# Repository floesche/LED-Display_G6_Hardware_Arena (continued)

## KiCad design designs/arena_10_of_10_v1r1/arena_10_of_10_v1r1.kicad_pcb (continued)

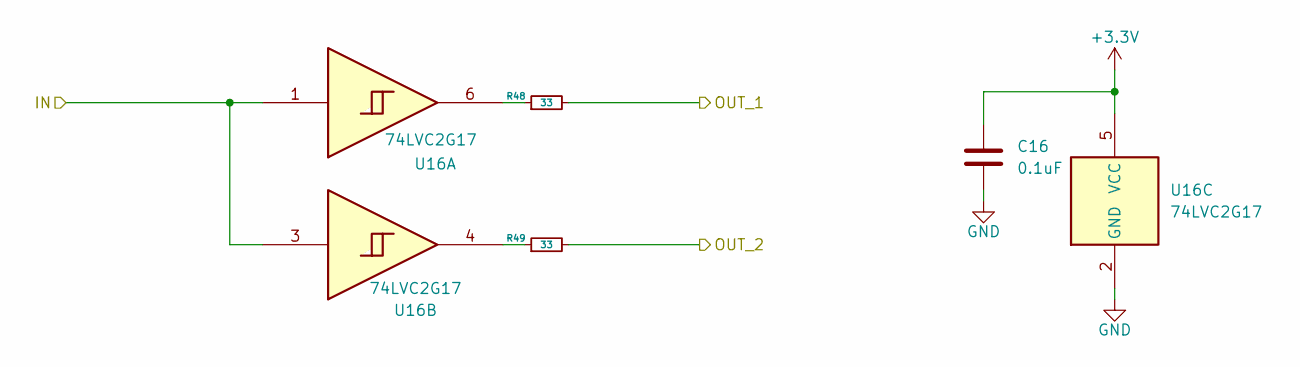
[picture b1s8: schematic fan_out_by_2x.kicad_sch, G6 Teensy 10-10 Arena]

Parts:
C16: 0.1uF; C_0402_1005Metric; LCSC Part # C1525
R48, R49: 33; R_0402_1005Metric; LCSC Part # C25105
U16: 74LVC2G17; SOT-23-6; LCSC Part # C7394037

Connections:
+3.3V: C16.1, U16.5 (VCC); also elsewhere on the board
/Fan Out/PAN.CS_00_P1: R48.2; also elsewhere on the board
/Fan Out/PAN.CS_00_P6: R49.2; also elsewhere on the board
/Fan Out/TNY.CS_00: U16.1, U16.3; also elsewhere on the board
unnamed: R48.1, U16.6
unnamed: R49.1, U16.4

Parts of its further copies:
C17, C18, C19, C20, C21, C22, C23, C24, C25, C26, C27, C28, C29, C30, C31, C32, C33, C34, C35: 0.1uF; C_0402_1005Metric; LCSC Part # C1525
R50, R51, R52, R53, R54, R55, R56, R57, R58, R59, R60, R61, R62, R63, R64, R65, R66, R67, R68, R69, R70, R71, R72, R73, R74, R75, R76, R77, R78, R79, R80, R81, R82, R83, R84, R85, R86, R87: 33; R_0402_1005Metric; LCSC Part # C25105
U17, U18, U19, U20, U21, U22, U23, U24, U25, U26, U27, U28, U29, U30, U31, U32, U33, U34, U35: 74LVC2G17; SOT-23-6; LCSC Part # C7394037

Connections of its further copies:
+3.3V: C17.1, C18.1, C19.1, C20.1, C21.1, C22.1, C23.1, C24.1, C25.1, C26.1, C27.1, C28.1, C29.1, C30.1, C31.1, C32.1, C33.1, C34.1, C35.1, U17.5 (VCC), U18.5 (VCC), U19.5 (VCC), U20.5 (VCC), U21.5 (VCC), U22.5 (VCC), U23.5 (VCC), U24.5 (VCC), U25.5 (VCC), U26.5 (VCC), U27.5 (VCC), U28.5 (VCC), U29.5 (VCC), U30.5 (VCC), U31.5 (VCC), U32.5 (VCC), U33.5 (VCC), U34.5 (VCC), U35.5 (VCC); also elsewhere on the board
/Fan Out/PAN.CS_01_P1: R50.2; also elsewhere on the board
/Fan Out/PAN.CS_01_P6: R51.2; also elsewhere on the board
/Fan Out/PAN.CS_02_P1: R52.2; also elsewhere on the board
/Fan Out/PAN.CS_02_P6: R53.2; also elsewhere on the board
/Fan Out/PAN.CS_03_P1: R54.2; also elsewhere on the board
/Fan Out/PAN.CS_03_P6: R55.2; also elsewhere on the board
/Fan Out/PAN.CS_04_P2: R56.2; also elsewhere on the board
/Fan Out/PAN.CS_04_P7: R57.2; also elsewhere on the board
/Fan Out/PAN.CS_05_P2: R58.2; also elsewhere on the board
/Fan Out/PAN.CS_05_P7: R59.2; also elsewhere on the board
/Fan Out/PAN.CS_06_P2: R60.2; also elsewhere on the board
/Fan Out/PAN.CS_06_P7: R61.2; also elsewhere on the board
/Fan Out/PAN.CS_07_P2: R62.2; also elsewhere on the board
/Fan Out/PAN.CS_07_P7: R63.2; also elsewhere on the board
/Fan Out/PAN.CS_08_P3: R64.2; also elsewhere on the board
/Fan Out/PAN.CS_08_P8: R65.2; also elsewhere on the board
/Fan Out/PAN.CS_09_P3: R66.2; also elsewhere on the board
/Fan Out/PAN.CS_09_P8: R67.2; also elsewhere on the board
/Fan Out/PAN.CS_10_P3: R68.2; also elsewhere on the board
/Fan Out/PAN.CS_10_P8: R69.2; also elsewhere on the board
/Fan Out/PAN.CS_11_P3: R70.2; also elsewhere on the board
/Fan Out/PAN.CS_11_P8: R71.2; also elsewhere on the board
/Fan Out/PAN.CS_12_P4: R72.2; also elsewhere on the board
/Fan Out/PAN.CS_12_P9: R73.2; also elsewhere on the board
/Fan Out/PAN.CS_13_P4: R74.2; also elsewhere on the board
/Fan Out/PAN.CS_13_P9: R75.2; also elsewhere on the board
/Fan Out/PAN.CS_14_P4: R76.2; also elsewhere on the board
/Fan Out/PAN.CS_14_P9: R77.2; also elsewhere on the board
/Fan Out/PAN.CS_15_P4: R78.2; also elsewhere on the board
/Fan Out/PAN.CS_15_P9: R79.2; also elsewhere on the board
/Fan Out/PAN.CS_16_P5: R80.2; also elsewhere on the board
/Fan Out/PAN.CS_16_P10: R81.2; also elsewhere on the board
/Fan Out/PAN.CS_17_P5: R82.2; also elsewhere on the board
/Fan Out/PAN.CS_17_P10: R83.2; also elsewhere on the board
/Fan Out/PAN.CS_18_P5: R84.2; also elsewhere on the board
/Fan Out/PAN.CS_18_P10: R85.2; also elsewhere on the board
/Fan Out/PAN.CS_19_P5: R86.2; also elsewhere on the board
/Fan Out/PAN.CS_19_P10: R87.2; also elsewhere on the board
/Fan Out/TNY.CS_01: U17.1, U17.3; also elsewhere on the board
/Fan Out/TNY.CS_02: U18.1, U18.3; also elsewhere on the board
/Fan Out/TNY.CS_03: U19.1, U19.3; also elsewhere on the board
/Fan Out/TNY.CS_04: U20.1, U20.3; also elsewhere on the board
/Fan Out/TNY.CS_05: U21.1, U21.3; also elsewhere on the board
/Fan Out/TNY.CS_06: U22.1, U22.3; also elsewhere on the board
/Fan Out/TNY.CS_07: U23.1, U23.3; also elsewhere on the board
/Fan Out/TNY.CS_08: U24.1, U24.3; also elsewhere on the board
/Fan Out/TNY.CS_09: U25.1, U25.3; also elsewhere on the board
/Fan Out/TNY.CS_10: U26.1, U26.3; also elsewhere on the board
/Fan Out/TNY.CS_11: U27.1, U27.3; also elsewhere on the board
/Fan Out/TNY.CS_12: U28.1, U28.3; also elsewhere on the board
/Fan Out/TNY.CS_13: U29.1, U29.3; also elsewhere on the board
/Fan Out/TNY.CS_14: U30.1, U30.3; also elsewhere on the board
/Fan Out/TNY.CS_15: U31.1, U31.3; also elsewhere on the board
/Fan Out/TNY.CS_16: U32.1, U32.3; also elsewhere on the board
/Fan Out/TNY.CS_17: U33.1, U33.3; also elsewhere on the board
/Fan Out/TNY.CS_18: U34.1, U34.3; also elsewhere on the board
/Fan Out/TNY.CS_19: U35.1, U35.3; also elsewhere on the board
unnamed: R50.1, U17.6
unnamed: R51.1, U17.4
unnamed: R52.1, U18.6
unnamed: R53.1, U18.4
unnamed: R54.1, U19.6
unnamed: R55.1, U19.4
unnamed: R56.1, U20.6
unnamed: R57.1, U20.4
unnamed: R58.1, U21.6
unnamed: R59.1, U21.4
unnamed: R60.1, U22.6
unnamed: R61.1, U22.4
unnamed: R62.1, U23.6
unnamed: R63.1, U23.4
unnamed: R64.1, U24.6
unnamed: R65.1, U24.4
unnamed: R66.1, U25.6
unnamed: R67.1, U25.4
unnamed: R68.1, U26.6
unnamed: R69.1, U26.4
unnamed: R70.1, U27.6
unnamed: R71.1, U27.4
unnamed: R72.1, U28.6
unnamed: R73.1, U28.4
unnamed: R74.1, U29.6
unnamed: R75.1, U29.4
unnamed: R76.1, U30.6
unnamed: R77.1, U30.4
unnamed: R78.1, U31.6
unnamed: R79.1, U31.4
unnamed: R80.1, U32.6
unnamed: R81.1, U32.4
unnamed: R82.1, U33.6
unnamed: R83.1, U33.4
unnamed: R84.1, U34.6
unnamed: R85.1, U34.4
unnamed: R86.1, U35.6
unnamed: R87.1, U35.4

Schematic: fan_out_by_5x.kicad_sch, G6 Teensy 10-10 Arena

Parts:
C4, C5, C6: 0.1uF; C_0402_1005Metric; LCSC Part # C1525
R28, R29, R30, R31, R32: 33; R_0402_1005Metric; LCSC Part # C25105
U4, U5, U6: 74LVC2G17; SOT-23-6; LCSC Part # C7394037

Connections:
+3.3V: C4.1, C5.1, C6.1, U4.5 (VCC), U5.5 (VCC), U6.5 (VCC); also elsewhere on the board
/Fan Out/PAN.SCK_B0_P1: R28.2; also elsewhere on the board
/Fan Out/PAN.SCK_B0_P2: R29.2; also elsewhere on the board
/Fan Out/PAN.SCK_B0_P3: R30.2; also elsewhere on the board
/Fan Out/PAN.SCK_B0_P4: R31.2; also elsewhere on the board
/Fan Out/PAN.SCK_B0_P5: R32.2; also elsewhere on the board
/Fan Out/TNY.SCK_B0: U4.1, U4.3, U5.1, U5.3, U6.1; also elsewhere on the board
unnamed: R28.1, U4.6
unnamed: R29.1, U4.4
unnamed: R30.1, U5.6
unnamed: R31.1, U5.4
unnamed: R32.1, U6.6

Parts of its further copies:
C7, C8, C9, C10, C11, C12, C13, C14, C15, C36, C37, C38, C39, C40, C41: 0.1uF; C_0402_1005Metric; LCSC Part # C1525
R33, R34, R35, R36, R37, R38, R39, R40, R41, R42, R43, R44, R45, R46, R47, R88, R89, R90, R91, R92, R93, R94, R95, R96, R97: 33; R_0402_1005Metric; LCSC Part # C25105
U7, U8, U9, U10, U11, U12, U13, U14, U15, U36, U37, U38, U39, U40, U41: 74LVC2G17; SOT-23-6; LCSC Part # C7394037

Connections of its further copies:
+3.3V: C7.1, C8.1, C9.1, C10.1, C11.1, C12.1, C13.1, C14.1, C15.1, C36.1, C37.1, C38.1, C39.1, C40.1, C41.1, U7.5 (VCC), U8.5 (VCC), U9.5 (VCC), U10.5 (VCC), U11.5 (VCC), U12.5 (VCC), U13.5 (VCC), U14.5 (VCC), U15.5 (VCC), U36.5 (VCC), U37.5 (VCC), U38.5 (VCC), U39.5 (VCC), U40.5 (VCC), U41.5 (VCC); also elsewhere on the board
/Fan Out/PAN.EINT_P1: R93.2; also elsewhere on the board
/Fan Out/PAN.EINT_P2: R94.2; also elsewhere on the board
/Fan Out/PAN.EINT_P3: R95.2; also elsewhere on the board
/Fan Out/PAN.EINT_P4: R96.2; also elsewhere on the board
/Fan Out/PAN.EINT_P5: R97.2; also elsewhere on the board
/Fan Out/PAN.EINT_P6: R88.2; also elsewhere on the board
/Fan Out/PAN.EINT_P7: R89.2; also elsewhere on the board
/Fan Out/PAN.EINT_P8: R90.2; also elsewhere on the board
/Fan Out/PAN.EINT_P9: R91.2; also elsewhere on the board
/Fan Out/PAN.EINT_P10: R92.2; also elsewhere on the board
/Fan Out/PAN.MOSI_B0_P1: R33.2; also elsewhere on the board
/Fan Out/PAN.MOSI_B0_P2: R34.2; also elsewhere on the board
/Fan Out/PAN.MOSI_B0_P3: R35.2; also elsewhere on the board
/Fan Out/PAN.MOSI_B0_P4: R36.2; also elsewhere on the board
/Fan Out/PAN.MOSI_B0_P5: R37.2; also elsewhere on the board
/Fan Out/PAN.MOSI_B1_P6: R43.2; also elsewhere on the board
/Fan Out/PAN.MOSI_B1_P7: R44.2; also elsewhere on the board
/Fan Out/PAN.MOSI_B1_P8: R45.2; also elsewhere on the board
/Fan Out/PAN.MOSI_B1_P9: R46.2; also elsewhere on the board
/Fan Out/PAN.MOSI_B1_P10: R47.2; also elsewhere on the board
/Fan Out/PAN.SCK_B1_P6: R38.2; also elsewhere on the board
/Fan Out/PAN.SCK_B1_P7: R39.2; also elsewhere on the board
/Fan Out/PAN.SCK_B1_P8: R40.2; also elsewhere on the board
/Fan Out/PAN.SCK_B1_P9: R41.2; also elsewhere on the board
/Fan Out/PAN.SCK_B1_P10: R42.2; also elsewhere on the board
/Fan Out/TNY.EINT: U36.1, U36.3, U37.1, U37.3, U38.1, U39.1, U39.3, U40.1, U40.3, U41.1; also elsewhere on the board
/Fan Out/TNY.MOSI_B0: U7.1, U7.3, U8.1, U8.3, U9.1; also elsewhere on the board
/Fan Out/TNY.MOSI_B1: U13.1, U13.3, U14.1, U14.3, U15.1; also elsewhere on the board
/Fan Out/TNY.SCK_B1: U10.1, U10.3, U11.1, U11.3, U12.1; also elsewhere on the board
unnamed: R33.1, U7.6
unnamed: R34.1, U7.4
unnamed: R35.1, U8.6
unnamed: R36.1, U8.4
unnamed: R37.1, U9.6
unnamed: R38.1, U10.6
unnamed: R39.1, U10.4
unnamed: R40.1, U11.6
unnamed: R41.1, U11.4
unnamed: R42.1, U12.6
unnamed: R43.1, U13.6
unnamed: R44.1, U13.4
unnamed: R45.1, U14.6
unnamed: R46.1, U14.4
unnamed: R47.1, U15.6
unnamed: R88.1, U36.6
unnamed: R89.1, U36.4
unnamed: R90.1, U37.6
unnamed: R91.1, U37.4
unnamed: R92.1, U38.6
unnamed: R93.1, U39.6
unnamed: R94.1, U39.4
unnamed: R95.1, U40.6
unnamed: R96.1, U40.4
unnamed: R97.1, U41.6

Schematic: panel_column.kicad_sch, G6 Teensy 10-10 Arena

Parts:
C42: 100uF; C_1210_3225Metric; LCSC Part # C7432790
J5, J6: Conn_01x05; PinSocket_1x05_P2.54mm_Vertical; LCSC Part # C50950
P1: NA; Panel_Silk; not fitted

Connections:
/Panels/Panel Column P1/Column Buffer/CS0_OUT: J6.1; also elsewhere on the board
/Panels/Panel Column P1/Column Buffer/CS1_OUT: J6.2; also elsewhere on the board
/Panels/Panel Column P1/Column Buffer/CS2_OUT: J6.3; also elsewhere on the board
/Panels/Panel Column P1/Column Buffer/CS_3OUT: J6.4; also elsewhere on the board
/Panels/Panel Column P1/Column Buffer/EINT_OUT: J6.5; also elsewhere on the board
/Panels/Panel Column P1/Column Buffer/MISO_IN: J5.5; also elsewhere on the board
/Panels/Panel Column P1/Column Buffer/MOSI_OUT: J5.4; also elsewhere on the board
/Panels/Panel Column P1/Column Buffer/SCK_OUT: J5.3; also elsewhere on the board

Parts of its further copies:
C47, C52, C57, C62, C67, C72, C77, C82, C87: 100uF; C_1210_3225Metric; LCSC Part # C7432790
J7, J8, J9, J10, J11, J12, J13, J14, J15, J16, J17, J18, J19, J20, J21, J22, J23, J24: Conn_01x05; PinSocket_1x05_P2.54mm_Vertical; LCSC Part # C50950
P2, P3, P4, P5, P6, P7, P8, P9, P10: NA; Panel_Silk; not fitted

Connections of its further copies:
/Panels/Panel Column P2/Column Buffer/CS0_OUT: J8.1; also elsewhere on the board
/Panels/Panel Column P2/Column Buffer/CS1_OUT: J8.2; also elsewhere on the board
/Panels/Panel Column P2/Column Buffer/CS2_OUT: J8.3; also elsewhere on the board
/Panels/Panel Column P2/Column Buffer/CS_3OUT: J8.4; also elsewhere on the board
/Panels/Panel Column P2/Column Buffer/EINT_OUT: J8.5; also elsewhere on the board
/Panels/Panel Column P2/Column Buffer/MISO_IN: J7.5; also elsewhere on the board
/Panels/Panel Column P2/Column Buffer/MOSI_OUT: J7.4; also elsewhere on the board
/Panels/Panel Column P2/Column Buffer/SCK_OUT: J7.3; also elsewhere on the board
/Panels/Panel Column P3/Column Buffer/CS0_OUT: J10.1; also elsewhere on the board
/Panels/Panel Column P3/Column Buffer/CS1_OUT: J10.2; also elsewhere on the board
/Panels/Panel Column P3/Column Buffer/CS2_OUT: J10.3; also elsewhere on the board
/Panels/Panel Column P3/Column Buffer/CS_3OUT: J10.4; also elsewhere on the board
/Panels/Panel Column P3/Column Buffer/EINT_OUT: J10.5; also elsewhere on the board
/Panels/Panel Column P3/Column Buffer/MISO_IN: J9.5; also elsewhere on the board
/Panels/Panel Column P3/Column Buffer/MOSI_OUT: J9.4; also elsewhere on the board
/Panels/Panel Column P3/Column Buffer/SCK_OUT: J9.3; also elsewhere on the board
/Panels/Panel Column P4/Column Buffer/CS0_OUT: J12.1; also elsewhere on the board
/Panels/Panel Column P4/Column Buffer/CS1_OUT: J12.2; also elsewhere on the board
/Panels/Panel Column P4/Column Buffer/CS2_OUT: J12.3; also elsewhere on the board
/Panels/Panel Column P4/Column Buffer/CS_3OUT: J12.4; also elsewhere on the board
/Panels/Panel Column P4/Column Buffer/EINT_OUT: J12.5; also elsewhere on the board
/Panels/Panel Column P4/Column Buffer/MISO_IN: J11.5; also elsewhere on the board
/Panels/Panel Column P4/Column Buffer/MOSI_OUT: J11.4; also elsewhere on the board
/Panels/Panel Column P4/Column Buffer/SCK_OUT: J11.3; also elsewhere on the board
/Panels/Panel Column P5/Column Buffer/CS0_OUT: J14.1; also elsewhere on the board
/Panels/Panel Column P5/Column Buffer/CS1_OUT: J14.2; also elsewhere on the board
/Panels/Panel Column P5/Column Buffer/CS2_OUT: J14.3; also elsewhere on the board
/Panels/Panel Column P5/Column Buffer/CS_3OUT: J14.4; also elsewhere on the board
/Panels/Panel Column P5/Column Buffer/EINT_OUT: J14.5; also elsewhere on the board
/Panels/Panel Column P5/Column Buffer/MISO_IN: J13.5; also elsewhere on the board
/Panels/Panel Column P5/Column Buffer/MOSI_OUT: J13.4; also elsewhere on the board
/Panels/Panel Column P5/Column Buffer/SCK_OUT: J13.3; also elsewhere on the board
/Panels/Panel Column P6/Column Buffer/CS0_OUT: J16.1; also elsewhere on the board
/Panels/Panel Column P6/Column Buffer/CS1_OUT: J16.2; also elsewhere on the board
/Panels/Panel Column P6/Column Buffer/CS2_OUT: J16.3; also elsewhere on the board
/Panels/Panel Column P6/Column Buffer/CS_3OUT: J16.4; also elsewhere on the board
/Panels/Panel Column P6/Column Buffer/EINT_OUT: J16.5; also elsewhere on the board
/Panels/Panel Column P6/Column Buffer/MISO_IN: J15.5; also elsewhere on the board
/Panels/Panel Column P6/Column Buffer/MOSI_OUT: J15.4; also elsewhere on the board
/Panels/Panel Column P6/Column Buffer/SCK_OUT: J15.3; also elsewhere on the board
/Panels/Panel Column P7/Column Buffer/CS0_OUT: J18.1; also elsewhere on the board
/Panels/Panel Column P7/Column Buffer/CS1_OUT: J18.2; also elsewhere on the board
/Panels/Panel Column P7/Column Buffer/CS2_OUT: J18.3; also elsewhere on the board
/Panels/Panel Column P7/Column Buffer/CS_3OUT: J18.4; also elsewhere on the board
/Panels/Panel Column P7/Column Buffer/EINT_OUT: J18.5; also elsewhere on the board
/Panels/Panel Column P7/Column Buffer/MISO_IN: J17.5; also elsewhere on the board
/Panels/Panel Column P7/Column Buffer/MOSI_OUT: J17.4; also elsewhere on the board
/Panels/Panel Column P7/Column Buffer/SCK_OUT: J17.3; also elsewhere on the board
/Panels/Panel Column P8/Column Buffer/CS0_OUT: J20.1; also elsewhere on the board
/Panels/Panel Column P8/Column Buffer/CS1_OUT: J20.2; also elsewhere on the board
/Panels/Panel Column P8/Column Buffer/CS2_OUT: J20.3; also elsewhere on the board
/Panels/Panel Column P8/Column Buffer/CS_3OUT: J20.4; also elsewhere on the board
/Panels/Panel Column P8/Column Buffer/EINT_OUT: J20.5; also elsewhere on the board
/Panels/Panel Column P8/Column Buffer/MISO_IN: J19.5; also elsewhere on the board
/Panels/Panel Column P8/Column Buffer/MOSI_OUT: J19.4; also elsewhere on the board
/Panels/Panel Column P8/Column Buffer/SCK_OUT: J19.3; also elsewhere on the board
/Panels/Panel Column P9/Column Buffer/CS0_OUT: J22.1; also elsewhere on the board
/Panels/Panel Column P9/Column Buffer/CS1_OUT: J22.2; also elsewhere on the board
/Panels/Panel Column P9/Column Buffer/CS2_OUT: J22.3; also elsewhere on the board
/Panels/Panel Column P9/Column Buffer/CS_3OUT: J22.4; also elsewhere on the board
/Panels/Panel Column P9/Column Buffer/EINT_OUT: J22.5; also elsewhere on the board
/Panels/Panel Column P9/Column Buffer/MISO_IN: J21.5; also elsewhere on the board
/Panels/Panel Column P9/Column Buffer/MOSI_OUT: J21.4; also elsewhere on the board
/Panels/Panel Column P9/Column Buffer/SCK_OUT: J21.3; also elsewhere on the board
/Panels/Panel Column P10/Column Buffer/CS0_OUT: J24.1; also elsewhere on the board
/Panels/Panel Column P10/Column Buffer/CS1_OUT: J24.2; also elsewhere on the board
/Panels/Panel Column P10/Column Buffer/CS2_OUT: J24.3; also elsewhere on the board
/Panels/Panel Column P10/Column Buffer/CS_3OUT: J24.4; also elsewhere on the board
/Panels/Panel Column P10/Column Buffer/EINT_OUT: J24.5; also elsewhere on the board
/Panels/Panel Column P10/Column Buffer/MISO_IN: J23.5; also elsewhere on the board
/Panels/Panel Column P10/Column Buffer/MOSI_OUT: J23.4; also elsewhere on the board
/Panels/Panel Column P10/Column Buffer/SCK_OUT: J23.3; also elsewhere on the board

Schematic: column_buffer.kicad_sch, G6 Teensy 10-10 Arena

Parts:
C43, C44, C45, C46: 0.1uF; C_0402_1005Metric; LCSC Part # C1525
R98, R99, R100, R101, R102, R103, R104, R105: 33; R_0402_1005Metric; LCSC Part # C25105
U42, U43, U44, U45: 74LVC2G17; SOT-23-6; LCSC Part # C7394037

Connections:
+3.3V: C43.1, C44.1, C45.1, C46.1, U42.5 (VCC), U43.5 (VCC), U44.5 (VCC), U45.5 (VCC); also elsewhere on the board
/Fan Out/PAN.CS_00_P1: U43.3; also elsewhere on the board
/Fan Out/PAN.CS_01_P1: U44.1; also elsewhere on the board
/Fan Out/PAN.CS_02_P1: U44.3; also elsewhere on the board
/Fan Out/PAN.CS_03_P1: U45.1; also elsewhere on the board
/Fan Out/PAN.EINT_P1: U45.3; also elsewhere on the board
/Fan Out/PAN.MISO_B0_P1: R98.2; also elsewhere on the board
/Fan Out/PAN.MOSI_B0_P1: U42.3; also elsewhere on the board
/Fan Out/PAN.SCK_B0_P1: U42.1; also elsewhere on the board
/Panels/Panel Column P1/Column Buffer/CS0_OUT: R101.2; also elsewhere on the board
/Panels/Panel Column P1/Column Buffer/CS1_OUT: R102.2; also elsewhere on the board
/Panels/Panel Column P1/Column Buffer/CS2_OUT: R103.2; also elsewhere on the board
/Panels/Panel Column P1/Column Buffer/CS_3OUT: R104.2; also elsewhere on the board
/Panels/Panel Column P1/Column Buffer/EINT_OUT: R105.2; also elsewhere on the board
/Panels/Panel Column P1/Column Buffer/MISO_IN: U43.1; also elsewhere on the board
/Panels/Panel Column P1/Column Buffer/MOSI_OUT: R100.2; also elsewhere on the board
/Panels/Panel Column P1/Column Buffer/SCK_OUT: R99.2; also elsewhere on the board
unnamed: R98.1, U43.6
unnamed: R99.1, U42.6
unnamed: R100.1, U42.4
unnamed: R101.1, U43.4
unnamed: R102.1, U44.6
unnamed: R103.1, U44.4
unnamed: R104.1, U45.6
unnamed: R105.1, U45.4

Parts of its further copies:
C48, C49, C50, C51, C53, C54, C55, C56, C58, C59, C60, C61, C63, C64, C65, C66, C68, C69, C70, C71, C73, C74, C75, C76, C78, C79, C80, C81, C83, C84, C85, C86, C88, C89, C90, C91: 0.1uF; C_0402_1005Metric; LCSC Part # C1525
R106, R107, R108, R109, R110, R111, R112, R113, R114, R115, R116, R117, R118, R119, R120, R121, R122, R123, R124, R125, R126, R127, R128, R129, R130, R131, R132, R133, R134, R135, R136, R137, R138, R139, R140, R141, R142, R143, R144, R145, R146, R147, R148, R149, R150, R151, R152, R153, R154, R155, R156, R157, R158, R159, R160, R161, R162, R163, R164, R165, R166, R167, R168, R169, R170, R171, R172, R173, R174, R175, R176, R177: 33; R_0402_1005Metric; LCSC Part # C25105
U46, U47, U48, U49, U50, U51, U52, U53, U54, U55, U56, U57, U58, U59, U60, U61, U62, U63, U64, U65, U66, U67, U68, U69, U70, U71, U72, U73, U74, U75, U76, U77, U78, U79, U80, U81: 74LVC2G17; SOT-23-6; LCSC Part # C7394037

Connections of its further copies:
+3.3V: C48.1, C49.1, C50.1, C51.1, C53.1, C54.1, C55.1, C56.1, C58.1, C59.1, C60.1, C61.1, C63.1, C64.1, C65.1, C66.1, C68.1, C69.1, C70.1, C71.1, C73.1, C74.1, C75.1, C76.1, C78.1, C79.1, C80.1, C81.1, C83.1, C84.1, C85.1, C86.1, C88.1, C89.1, C90.1, C91.1, U46.5 (VCC), U47.5 (VCC), U48.5 (VCC), U49.5 (VCC), U50.5 (VCC), U51.5 (VCC), U52.5 (VCC), U53.5 (VCC), U54.5 (VCC), U55.5 (VCC), U56.5 (VCC), U57.5 (VCC), U58.5 (VCC), U59.5 (VCC), U60.5 (VCC), U61.5 (VCC), U62.5 (VCC), U63.5 (VCC), U64.5 (VCC), U65.5 (VCC), U66.5 (VCC), U67.5 (VCC), U68.5 (VCC), U69.5 (VCC), U70.5 (VCC), U71.5 (VCC), U72.5 (VCC), U73.5 (VCC), U74.5 (VCC), U75.5 (VCC), U76.5 (VCC), U77.5 (VCC), U78.5 (VCC), U79.5 (VCC), U80.5 (VCC), U81.5 (VCC); also elsewhere on the board
/Fan Out/PAN.CS_00_P6: U63.3; also elsewhere on the board
/Fan Out/PAN.CS_01_P6: U64.1; also elsewhere on the board
/Fan Out/PAN.CS_02_P6: U64.3; also elsewhere on the board
/Fan Out/PAN.CS_03_P6: U65.1; also elsewhere on the board
/Fan Out/PAN.CS_04_P2: U47.3; also elsewhere on the board
/Fan Out/PAN.CS_04_P7: U67.3; also elsewhere on the board
/Fan Out/PAN.CS_05_P2: U48.1; also elsewhere on the board
/Fan Out/PAN.CS_05_P7: U68.1; also elsewhere on the board
/Fan Out/PAN.CS_06_P2: U48.3; also elsewhere on the board
/Fan Out/PAN.CS_06_P7: U68.3; also elsewhere on the board
/Fan Out/PAN.CS_07_P2: U49.1; also elsewhere on the board
/Fan Out/PAN.CS_07_P7: U69.1; also elsewhere on the board
/Fan Out/PAN.CS_08_P3: U51.3; also elsewhere on the board
/Fan Out/PAN.CS_08_P8: U71.3; also elsewhere on the board
/Fan Out/PAN.CS_09_P3: U52.1; also elsewhere on the board
/Fan Out/PAN.CS_09_P8: U72.1; also elsewhere on the board
/Fan Out/PAN.CS_10_P3: U52.3; also elsewhere on the board
/Fan Out/PAN.CS_10_P8: U72.3; also elsewhere on the board
/Fan Out/PAN.CS_11_P3: U53.1; also elsewhere on the board
/Fan Out/PAN.CS_11_P8: U73.1; also elsewhere on the board
/Fan Out/PAN.CS_12_P4: U55.3; also elsewhere on the board
/Fan Out/PAN.CS_12_P9: U75.3; also elsewhere on the board
/Fan Out/PAN.CS_13_P4: U56.1; also elsewhere on the board
/Fan Out/PAN.CS_13_P9: U76.1; also elsewhere on the board
/Fan Out/PAN.CS_14_P4: U56.3; also elsewhere on the board
/Fan Out/PAN.CS_14_P9: U76.3; also elsewhere on the board
/Fan Out/PAN.CS_15_P4: U57.1; also elsewhere on the board
/Fan Out/PAN.CS_15_P9: U77.1; also elsewhere on the board
/Fan Out/PAN.CS_16_P5: U59.3; also elsewhere on the board
/Fan Out/PAN.CS_16_P10: U79.3; also elsewhere on the board
/Fan Out/PAN.CS_17_P5: U60.1; also elsewhere on the board
/Fan Out/PAN.CS_17_P10: U80.1; also elsewhere on the board
/Fan Out/PAN.CS_18_P5: U60.3; also elsewhere on the board
/Fan Out/PAN.CS_18_P10: U80.3; also elsewhere on the board
/Fan Out/PAN.CS_19_P5: U61.1; also elsewhere on the board
/Fan Out/PAN.CS_19_P10: U81.1; also elsewhere on the board
/Fan Out/PAN.EINT_P2: U49.3; also elsewhere on the board
/Fan Out/PAN.EINT_P3: U53.3; also elsewhere on the board
/Fan Out/PAN.EINT_P4: U57.3; also elsewhere on the board
/Fan Out/PAN.EINT_P5: U61.3; also elsewhere on the board
/Fan Out/PAN.EINT_P6: U65.3; also elsewhere on the board
/Fan Out/PAN.EINT_P7: U69.3; also elsewhere on the board
/Fan Out/PAN.EINT_P8: U73.3; also elsewhere on the board
/Fan Out/PAN.EINT_P9: U77.3; also elsewhere on the board
/Fan Out/PAN.EINT_P10: U81.3; also elsewhere on the board
/Fan Out/PAN.MISO_B0_P2: R106.2; also elsewhere on the board
/Fan Out/PAN.MISO_B0_P3: R114.2; also elsewhere on the board
/Fan Out/PAN.MISO_B0_P4: R122.2; also elsewhere on the board
/Fan Out/PAN.MISO_B0_P5: R130.2; also elsewhere on the board
/Fan Out/PAN.MISO_B1_P6: R138.2; also elsewhere on the board
/Fan Out/PAN.MISO_B1_P7: R146.2; also elsewhere on the board
/Fan Out/PAN.MISO_B1_P8: R154.2; also elsewhere on the board
/Fan Out/PAN.MISO_B1_P9: R162.2; also elsewhere on the board
/Fan Out/PAN.MISO_B1_P10: R170.2; also elsewhere on the board
/Fan Out/PAN.MOSI_B0_P2: U46.3; also elsewhere on the board
/Fan Out/PAN.MOSI_B0_P3: U50.3; also elsewhere on the board
/Fan Out/PAN.MOSI_B0_P4: U54.3; also elsewhere on the board
/Fan Out/PAN.MOSI_B0_P5: U58.3; also elsewhere on the board
/Fan Out/PAN.MOSI_B1_P6: U62.3; also elsewhere on the board
/Fan Out/PAN.MOSI_B1_P7: U66.3; also elsewhere on the board
/Fan Out/PAN.MOSI_B1_P8: U70.3; also elsewhere on the board
/Fan Out/PAN.MOSI_B1_P9: U74.3; also elsewhere on the board
/Fan Out/PAN.MOSI_B1_P10: U78.3; also elsewhere on the board
/Fan Out/PAN.SCK_B0_P2: U46.1; also elsewhere on the board
/Fan Out/PAN.SCK_B0_P3: U50.1; also elsewhere on the board
/Fan Out/PAN.SCK_B0_P4: U54.1; also elsewhere on the board
/Fan Out/PAN.SCK_B0_P5: U58.1; also elsewhere on the board
/Fan Out/PAN.SCK_B1_P6: U62.1; also elsewhere on the board
/Fan Out/PAN.SCK_B1_P7: U66.1; also elsewhere on the board
/Fan Out/PAN.SCK_B1_P8: U70.1; also elsewhere on the board
/Fan Out/PAN.SCK_B1_P9: U74.1; also elsewhere on the board
/Fan Out/PAN.SCK_B1_P10: U78.1; also elsewhere on the board
/Panels/Panel Column P2/Column Buffer/CS0_OUT: R109.2; also elsewhere on the board
/Panels/Panel Column P2/Column Buffer/CS1_OUT: R110.2; also elsewhere on the board
/Panels/Panel Column P2/Column Buffer/CS2_OUT: R111.2; also elsewhere on the board
/Panels/Panel Column P2/Column Buffer/CS_3OUT: R112.2; also elsewhere on the board
/Panels/Panel Column P2/Column Buffer/EINT_OUT: R113.2; also elsewhere on the board
/Panels/Panel Column P2/Column Buffer/MISO_IN: U47.1; also elsewhere on the board
/Panels/Panel Column P2/Column Buffer/MOSI_OUT: R108.2; also elsewhere on the board
/Panels/Panel Column P2/Column Buffer/SCK_OUT: R107.2; also elsewhere on the board
/Panels/Panel Column P3/Column Buffer/CS0_OUT: R117.2; also elsewhere on the board
/Panels/Panel Column P3/Column Buffer/CS1_OUT: R118.2; also elsewhere on the board
/Panels/Panel Column P3/Column Buffer/CS2_OUT: R119.2; also elsewhere on the board
/Panels/Panel Column P3/Column Buffer/CS_3OUT: R120.2; also elsewhere on the board
/Panels/Panel Column P3/Column Buffer/EINT_OUT: R121.2; also elsewhere on the board
/Panels/Panel Column P3/Column Buffer/MISO_IN: U51.1; also elsewhere on the board
/Panels/Panel Column P3/Column Buffer/MOSI_OUT: R116.2; also elsewhere on the board
/Panels/Panel Column P3/Column Buffer/SCK_OUT: R115.2; also elsewhere on the board
/Panels/Panel Column P4/Column Buffer/CS0_OUT: R125.2; also elsewhere on the board
/Panels/Panel Column P4/Column Buffer/CS1_OUT: R126.2; also elsewhere on the board
/Panels/Panel Column P4/Column Buffer/CS2_OUT: R127.2; also elsewhere on the board
/Panels/Panel Column P4/Column Buffer/CS_3OUT: R128.2; also elsewhere on the board
/Panels/Panel Column P4/Column Buffer/EINT_OUT: R129.2; also elsewhere on the board
/Panels/Panel Column P4/Column Buffer/MISO_IN: U55.1; also elsewhere on the board
/Panels/Panel Column P4/Column Buffer/MOSI_OUT: R124.2; also elsewhere on the board
/Panels/Panel Column P4/Column Buffer/SCK_OUT: R123.2; also elsewhere on the board
/Panels/Panel Column P5/Column Buffer/CS0_OUT: R133.2; also elsewhere on the board
/Panels/Panel Column P5/Column Buffer/CS1_OUT: R134.2; also elsewhere on the board
/Panels/Panel Column P5/Column Buffer/CS2_OUT: R135.2; also elsewhere on the board
/Panels/Panel Column P5/Column Buffer/CS_3OUT: R136.2; also elsewhere on the board
/Panels/Panel Column P5/Column Buffer/EINT_OUT: R137.2; also elsewhere on the board
/Panels/Panel Column P5/Column Buffer/MISO_IN: U59.1; also elsewhere on the board
/Panels/Panel Column P5/Column Buffer/MOSI_OUT: R132.2; also elsewhere on the board
/Panels/Panel Column P5/Column Buffer/SCK_OUT: R131.2; also elsewhere on the board
/Panels/Panel Column P6/Column Buffer/CS0_OUT: R141.2; also elsewhere on the board
/Panels/Panel Column P6/Column Buffer/CS1_OUT: R142.2; also elsewhere on the board
/Panels/Panel Column P6/Column Buffer/CS2_OUT: R143.2; also elsewhere on the board
/Panels/Panel Column P6/Column Buffer/CS_3OUT: R144.2; also elsewhere on the board
/Panels/Panel Column P6/Column Buffer/EINT_OUT: R145.2; also elsewhere on the board
/Panels/Panel Column P6/Column Buffer/MISO_IN: U63.1; also elsewhere on the board
/Panels/Panel Column P6/Column Buffer/MOSI_OUT: R140.2; also elsewhere on the board
/Panels/Panel Column P6/Column Buffer/SCK_OUT: R139.2; also elsewhere on the board
/Panels/Panel Column P7/Column Buffer/CS0_OUT: R149.2; also elsewhere on the board
/Panels/Panel Column P7/Column Buffer/CS1_OUT: R150.2; also elsewhere on the board
/Panels/Panel Column P7/Column Buffer/CS2_OUT: R151.2; also elsewhere on the board
/Panels/Panel Column P7/Column Buffer/CS_3OUT: R152.2; also elsewhere on the board
/Panels/Panel Column P7/Column Buffer/EINT_OUT: R153.2; also elsewhere on the board
/Panels/Panel Column P7/Column Buffer/MISO_IN: U67.1; also elsewhere on the board
/Panels/Panel Column P7/Column Buffer/MOSI_OUT: R148.2; also elsewhere on the board
/Panels/Panel Column P7/Column Buffer/SCK_OUT: R147.2; also elsewhere on the board
/Panels/Panel Column P8/Column Buffer/CS0_OUT: R157.2; also elsewhere on the board
/Panels/Panel Column P8/Column Buffer/CS1_OUT: R158.2; also elsewhere on the board
/Panels/Panel Column P8/Column Buffer/CS2_OUT: R159.2; also elsewhere on the board
/Panels/Panel Column P8/Column Buffer/CS_3OUT: R160.2; also elsewhere on the board
/Panels/Panel Column P8/Column Buffer/EINT_OUT: R161.2; also elsewhere on the board
/Panels/Panel Column P8/Column Buffer/MISO_IN: U71.1; also elsewhere on the board
/Panels/Panel Column P8/Column Buffer/MOSI_OUT: R156.2; also elsewhere on the board
/Panels/Panel Column P8/Column Buffer/SCK_OUT: R155.2; also elsewhere on the board
/Panels/Panel Column P9/Column Buffer/CS0_OUT: R165.2; also elsewhere on the board
/Panels/Panel Column P9/Column Buffer/CS1_OUT: R166.2; also elsewhere on the board
/Panels/Panel Column P9/Column Buffer/CS2_OUT: R167.2; also elsewhere on the board
/Panels/Panel Column P9/Column Buffer/CS_3OUT: R168.2; also elsewhere on the board
/Panels/Panel Column P9/Column Buffer/EINT_OUT: R169.2; also elsewhere on the board
/Panels/Panel Column P9/Column Buffer/MISO_IN: U75.1; also elsewhere on the board
/Panels/Panel Column P9/Column Buffer/MOSI_OUT: R164.2; also elsewhere on the board
/Panels/Panel Column P9/Column Buffer/SCK_OUT: R163.2; also elsewhere on the board
/Panels/Panel Column P10/Column Buffer/CS0_OUT: R173.2; also elsewhere on the board
/Panels/Panel Column P10/Column Buffer/CS1_OUT: R174.2; also elsewhere on the board
/Panels/Panel Column P10/Column Buffer/CS2_OUT: R175.2; also elsewhere on the board
/Panels/Panel Column P10/Column Buffer/CS_3OUT: R176.2; also elsewhere on the board
/Panels/Panel Column P10/Column Buffer/EINT_OUT: R177.2; also elsewhere on the board
/Panels/Panel Column P10/Column Buffer/MISO_IN: U79.1; also elsewhere on the board
/Panels/Panel Column P10/Column Buffer/MOSI_OUT: R172.2; also elsewhere on the board
/Panels/Panel Column P10/Column Buffer/SCK_OUT: R171.2; also elsewhere on the board
unnamed: R106.1, U47.6
unnamed: R107.1, U46.6
unnamed: R108.1, U46.4
unnamed: R109.1, U47.4
unnamed: R110.1, U48.6
unnamed: R111.1, U48.4
unnamed: R112.1, U49.6
unnamed: R113.1, U49.4
unnamed: R114.1, U51.6
unnamed: R115.1, U50.6
unnamed: R116.1, U50.4
unnamed: R117.1, U51.4
unnamed: R118.1, U52.6
unnamed: R119.1, U52.4
unnamed: R120.1, U53.6
unnamed: R121.1, U53.4
unnamed: R122.1, U55.6
unnamed: R123.1, U54.6
unnamed: R124.1, U54.4
unnamed: R125.1, U55.4
unnamed: R126.1, U56.6
unnamed: R127.1, U56.4
unnamed: R128.1, U57.6
unnamed: R129.1, U57.4
unnamed: R130.1, U59.6
unnamed: R131.1, U58.6
unnamed: R132.1, U58.4
unnamed: R133.1, U59.4
unnamed: R134.1, U60.6
unnamed: R135.1, U60.4
unnamed: R136.1, U61.6
unnamed: R137.1, U61.4
unnamed: R138.1, U63.6
unnamed: R139.1, U62.6
unnamed: R140.1, U62.4
unnamed: R141.1, U63.4
unnamed: R142.1, U64.6
unnamed: R143.1, U64.4
unnamed: R144.1, U65.6
unnamed: R145.1, U65.4
unnamed: R146.1, U67.6
unnamed: R147.1, U66.6
unnamed: R148.1, U66.4
unnamed: R149.1, U67.4
unnamed: R150.1, U68.6
unnamed: R151.1, U68.4
unnamed: R152.1, U69.6
unnamed: R153.1, U69.4
unnamed: R154.1, U71.6
unnamed: R155.1, U70.6
unnamed: R156.1, U70.4
unnamed: R157.1, U71.4
unnamed: R158.1, U72.6
unnamed: R159.1, U72.4
unnamed: R160.1, U73.6
unnamed: R161.1, U73.4
unnamed: R162.1, U75.6
unnamed: R163.1, U74.6
unnamed: R164.1, U74.4
unnamed: R165.1, U75.4
unnamed: R166.1, U76.6
unnamed: R167.1, U76.4
unnamed: R168.1, U77.6
unnamed: R169.1, U77.4
unnamed: R170.1, U79.6
unnamed: R171.1, U78.6
unnamed: R172.1, U78.4
unnamed: R173.1, U79.4
unnamed: R174.1, U80.6
unnamed: R175.1, U80.4
unnamed: R176.1, U81.6
unnamed: R177.1, U81.4

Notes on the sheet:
SN74LVC1G125DRLR 296-18012-2-ND SN74HCS08BQAR 296-SN74HCS08BQARTR-ND

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
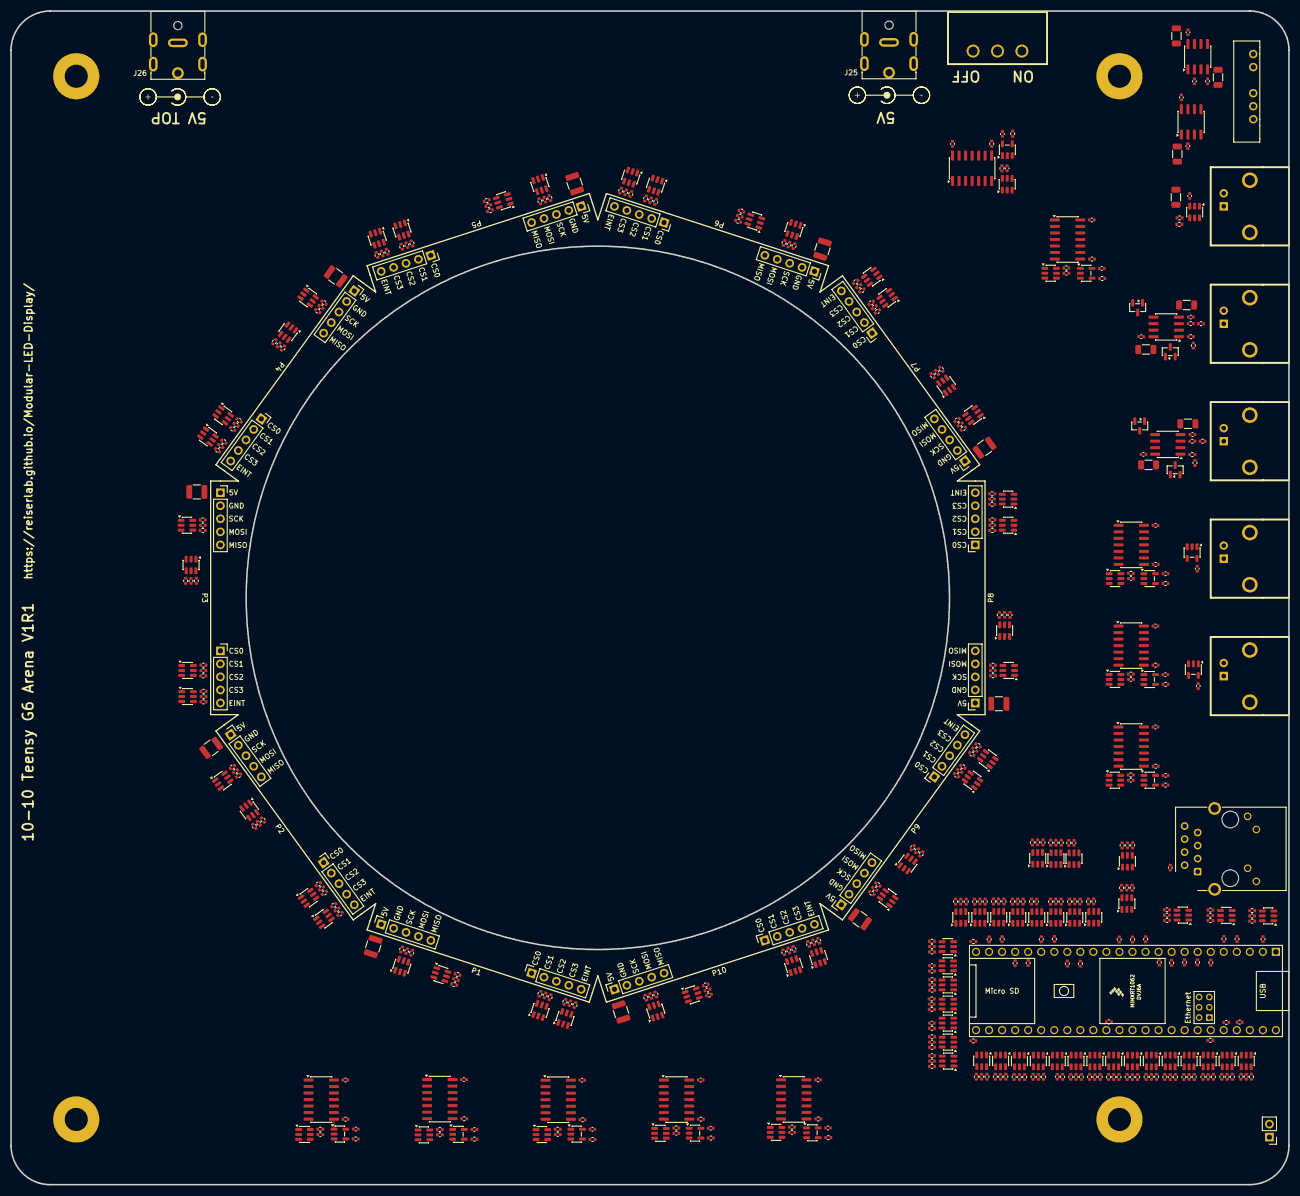
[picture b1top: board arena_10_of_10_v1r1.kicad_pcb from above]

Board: 6 copper layers, 248.9 x 228.6 mm, 519 parts (0 on the bottom side), 456 nets.

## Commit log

2026-04-14 Added keepout zones, power plane fills, and routing boundry.
2026-04-18 Finished 2nd completely routed PCB.
    For this board I modified the clearance matrix for the autorouter so
    that the there was always >= 0.3mm between traces.
2026-04-20 Cleaned up traces for 2nd routed board.
2026-04-22 Tightened DRC rules, increased via sizes, and added switch
    Added power switch SW1.
    Assemble pin sockets for Teensy (J100/J101, 1x24 pin sockets; J102, 2x3 pin socket, 2mm pitch for ethernet).
    Tightened board-setup DRC limits to match JLCPCB 6-layer minimums:
    - min_hole_to_hole 0.25 -> 0.5 mm,
    - min_text_thickness 0.08 -> 0.15 mm,
    - min_via_annular_width 0.05 -> 0.075 mm.
2026-04-23 disconnect SW1 pin 3
2026-05-22 Added design for arena top.
2026-06-01 Added parts to symbols files table for arena top.
2026-06-10 produced v1.1.7
2026-06-11 Update README with production version details
    Corrected a typo in the production update details and clarified the change to version 1.1.8.
